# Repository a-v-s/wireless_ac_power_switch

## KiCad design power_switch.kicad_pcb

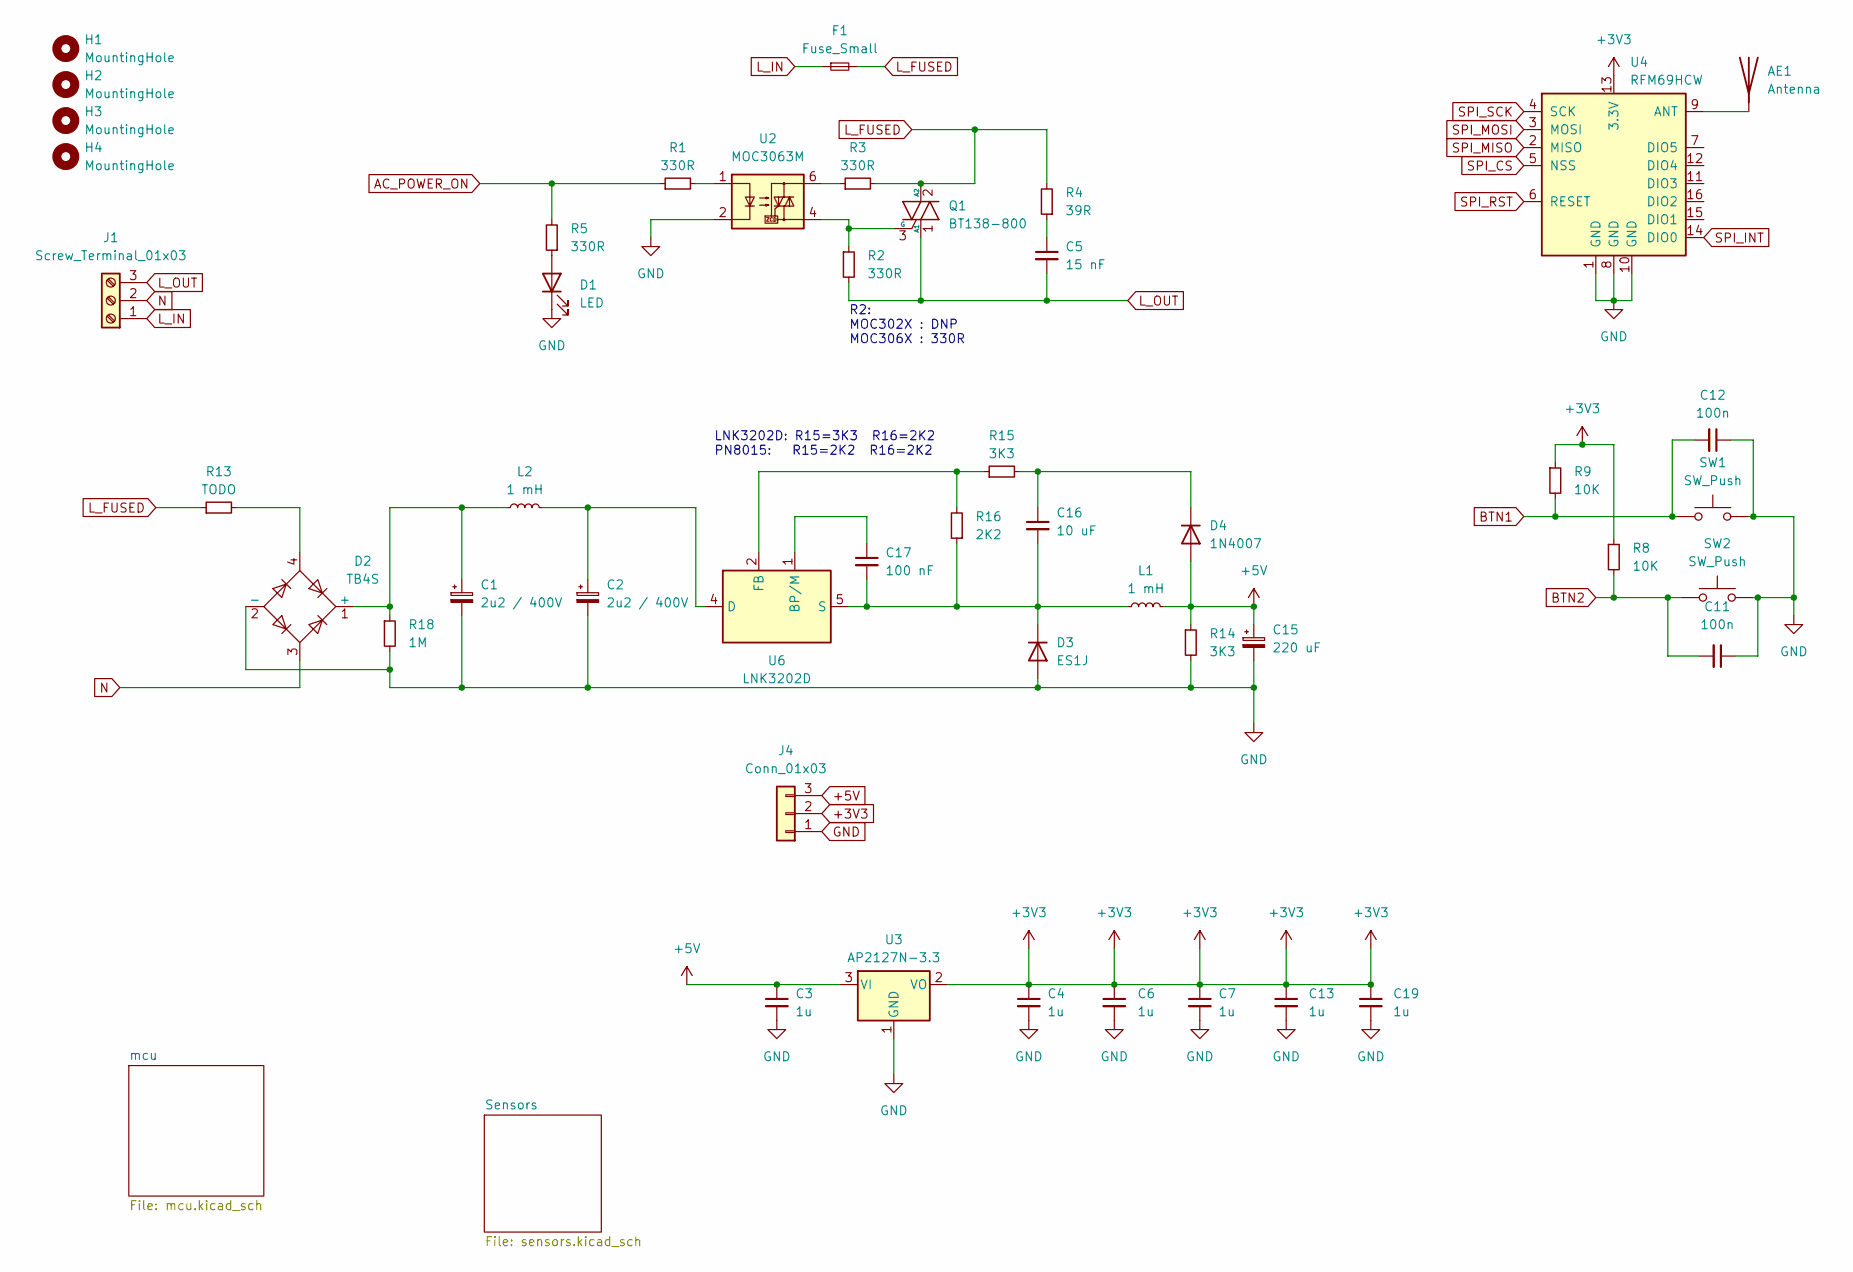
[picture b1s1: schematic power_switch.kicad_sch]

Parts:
AE1: Antenna; TestPoint_THTPad_D2.0mm_Drill1.0mm
C1, C2: 2u2 / 400V; CP_Elec_6.3x5.4
C3, C4, C6, C7, C13, C19: 1u; C_0805_2012Metric
C5: 15 nF; C_Rect_L11.0mm_W4.2mm_P10.00mm_MKT
C11, C12: 100n; C_0805_2012Metric
C15: 220 uF; CP_Elec_6.3x5.4
C16: 10 uF; C_0805_2012Metric
C17: 100 nF; C_0805_2012Metric
D1: LED; LED_0805_2012Metric
D2: TB4S; Diode_Bridge_Diotec_ABS
D3: ES1J; D_SMA
D4: 1N4007; D_SMA
F1: Fuse_Small; Fuseholder_Cylinder-5x20mm_Stelvio-Kontek_PTF78_Horizontal_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
H1, H2, H3, H4: MountingHole; MountingHole_2.2mm_M2
J1: Screw_Terminal_01x03; TerminalBlock_bornier-3_P5.08mm
J4: Conn_01x03; PinHeader_1x03_P2.54mm_Vertical
L1, L2: 1 mH; L_Changjiang_FNR8065S
Q1: BT138-800; TO-220-3_Vertical
R1, R5: 330R; R_0805_2012Metric
R2, R3: 330R; R_Axial_DIN0207_L6.3mm_D2.5mm_P10.16mm_Horizontal
R4: 39R; R_Axial_DIN0207_L6.3mm_D2.5mm_P10.16mm_Horizontal
R8, R9: 10K; R_0805_2012Metric
R13: TODO; R_Axial_DIN0309_L9.0mm_D3.2mm_P2.54mm_Vertical
R14, R15: 3K3; R_0805_2012Metric
R16: 2K2; R_0805_2012Metric
R18: 1M; R_1206_3216Metric
SW1, SW2: SW_Push; TS-1187
U2: MOC3063M; DIP-6_W7.62mm
U3: AP2127N-3.3; SOT-23
U4: RFM69HCW; HOPERF_RFM9XW_SMD
U6: LNK3202D; PowerIntegrations_SO-8C

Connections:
+3V3: C4.1, C6.1, C7.1, C13.1, C19.1, J4.2, R8.1, R9.1, U3.2 (VO), U4.13 (3.3V); also elsewhere on the board
+5V: C3.1, C15.1, D4.2 (A), J4.3, L1.2, R14.1, U3.3 (VI)
AC_POWER_ON: R1.1, R5.2; also elsewhere on the board
BTN1: C12.2, R9.2, SW1.2; also elsewhere on the board
BTN2: C11.2, R8.2, SW2.2; also elsewhere on the board
GND: C1.2, C2.2, C3.2, C4.2, C6.2, C7.2, C11.1, C12.1, C13.2, C15.2, C19.2, D1.1 (K), D2.2 (-), D3.2 (A), J4.1, R14.2, R18.2, SW1.1, SW2.1, U2.2, U3.1 (GND), U4.1 (GND), U4.8 (GND), U4.10 (GND); also elsewhere on the board
L_FUSED: F1.2, Q1.2 (A2), R3.2, R4.2, R13.1
L_IN: F1.1, J1.1
L_OUT: C5.2, J1.3, Q1.1 (A1), R2.2
N: D2.3, J1.2
unnamed: AE1.1 (A), U4.9 (ANT)
unnamed: C5.1, R4.1
unnamed: D1.2 (A), R5.1
unnamed: C1.1, D2.1 (+), L2.1, R18.1
unnamed: D2.4, R13.2
unnamed: C16.2, C17.2, D3.1 (K), L1.1, R16.1, U6.5 (S), U6.6 (S), U6.7 (S), U6.8 (S)
unnamed: C16.1, D4.1 (K), R15.2
unnamed: Q1.3 (G), R2.1, U2.4
unnamed: R1.2, U2.1
unnamed: R3.1, U2.6
unnamed: C17.1, U6.1 (BP/M)
unnamed: C2.1, L2.2, U6.4 (D)
unnamed: R15.1, R16.2, U6.2 (FB)
SPI_CS: U4.5 (NSS); also elsewhere on the board
SPI_INT: U4.14 (DIO0); also elsewhere on the board
SPI_MISO: U4.2 (MISO); also elsewhere on the board
SPI_MOSI: U4.3 (MOSI); also elsewhere on the board
SPI_RST: U4.6 (RESET); also elsewhere on the board
SPI_SCK: U4.4 (SCK); also elsewhere on the board

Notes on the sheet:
R2: MOC302X : DNP MOC306X : 330R
LNK3202D: R15=3K3 R16=2K2 PN8015: R15=2K2 R16=2K2

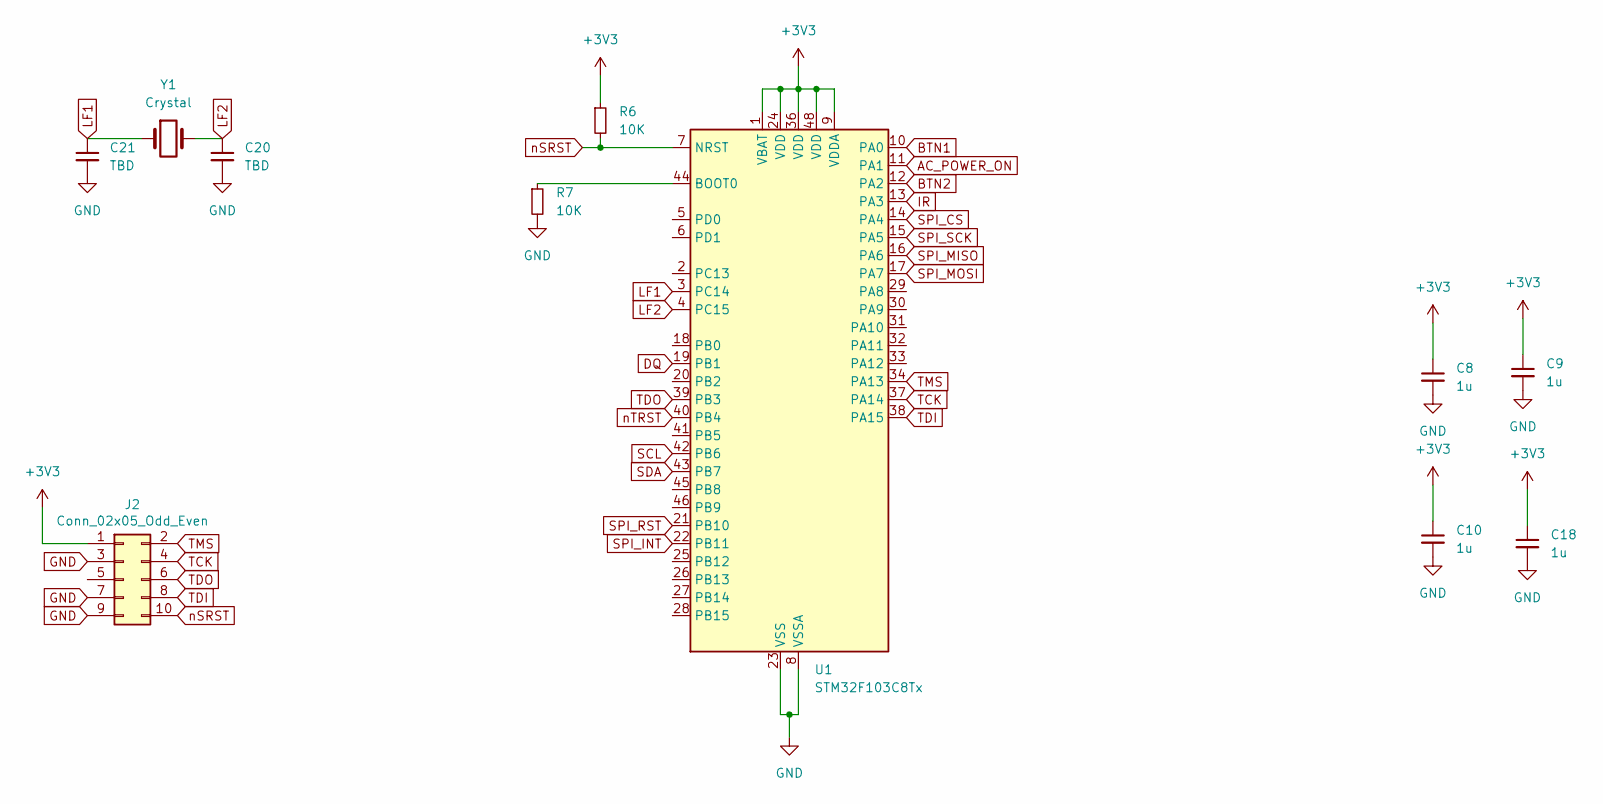
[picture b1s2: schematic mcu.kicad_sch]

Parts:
C8, C9, C10, C18: 1u; C_0805_2012Metric
C20, C21: TBD; C_0805_2012Metric
J2: Conn_02x05_Odd_Even; PinHeader_2x05_P1.27mm_Vertical_SMD
R6, R7: 10K; R_0805_2012Metric
U1: STM32F103C8Tx; LQFP-48_7x7mm_P0.5mm
Y1: Crystal; Crystal_SMD_3215-2Pin_3.2x1.5mm

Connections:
+3V3: C8.1, C9.1, C10.1, C18.1, J2.1, R6.1, U1.1 (VBAT), U1.9 (VDDA), U1.24 (VDD), U1.36 (VDD), U1.48 (VDD); also elsewhere on the board
AC_POWER_ON: U1.11 (PA1); also elsewhere on the board
BTN1: U1.10 (PA0); also elsewhere on the board
BTN2: U1.12 (PA2); also elsewhere on the board
DQ: U1.19 (PB1); also elsewhere on the board
GND: C8.2, C9.2, C10.2, C18.2, C20.2, C21.2, J2.3, J2.7, J2.9, R7.2, U1.8 (VSSA), U1.23 (VSS), U1.35 (VSS), U1.47 (VSS); also elsewhere on the board
IR: U1.13 (PA3); also elsewhere on the board
LF1: C21.1, U1.3 (PC14), Y1.1
LF2: C20.1, U1.4 (PC15), Y1.2
unnamed: R7.1, U1.44 (BOOT0)
SCL: U1.42 (PB6); also elsewhere on the board
SDA: U1.43 (PB7); also elsewhere on the board
SPI_CS: U1.14 (PA4); also elsewhere on the board
SPI_INT: U1.22 (PB11); also elsewhere on the board
SPI_MISO: U1.16 (PA6); also elsewhere on the board
SPI_MOSI: U1.17 (PA7); also elsewhere on the board
SPI_RST: U1.21 (PB10); also elsewhere on the board
SPI_SCK: U1.15 (PA5); also elsewhere on the board
TCK: J2.4, U1.37 (PA14)
TDI: J2.8, U1.38 (PA15)
TDO: J2.6, U1.39 (PB3)
TMS: J2.2, U1.34 (PA13)
nSRST: J2.10, R6.2, U1.7 (NRST)
nTRST: U1.40 (PB4)

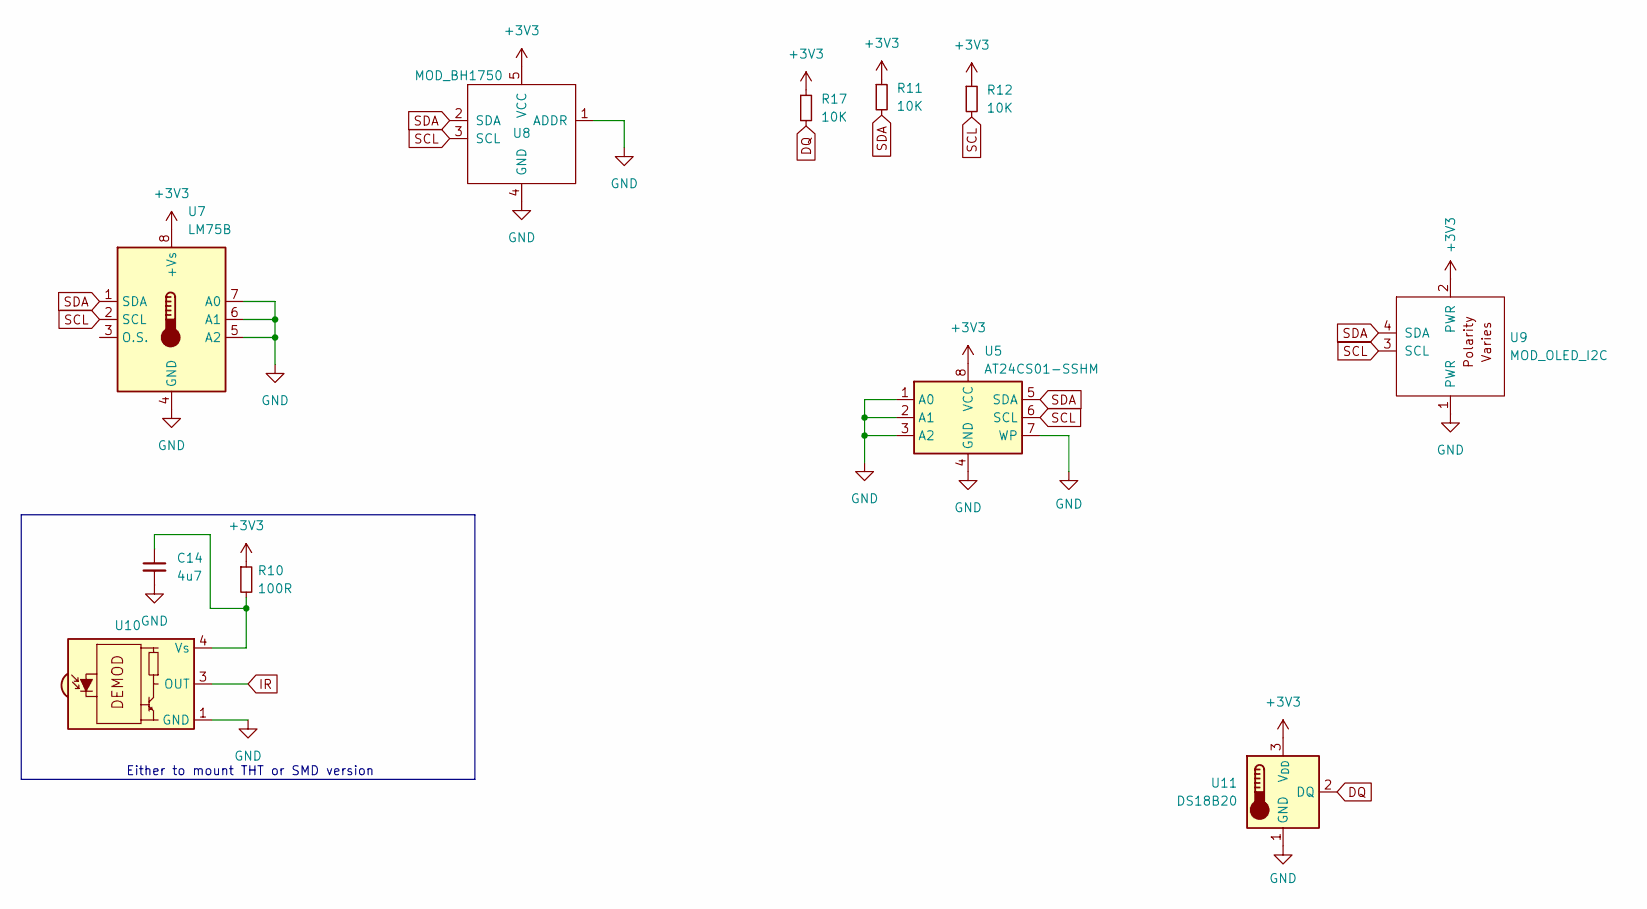
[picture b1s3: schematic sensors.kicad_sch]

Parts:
C14: 4u7; C_0805_2012Metric
R10: 100R; R_0805_2012Metric
R11, R12, R17: 10K; R_0805_2012Metric
U5: AT24CS01-SSHM; SOIC-8_3.9x4.9mm_P1.27mm
U7: LM75B; SO-8_3.9x4.9mm_P1.27mm
U8: MOD_BH1750
U9: MOD_OLED_I2C; MOD_OLED_I2C_128x64_0.96
U10: IRM-H6XXT-TR2
U11: DS18B20; TO-92_Inline

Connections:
+3V3: R10.1, R11.1, R12.1, R17.1, U5.8 (VCC), U7.8 (+Vs), U8.5 (VCC), U9.2 (PWR), U11.3 (V_{DD}); also elsewhere on the board
DQ: R17.2, U11.2 (DQ); also elsewhere on the board
GND: C14.2, U5.1 (A0), U5.2 (A1), U5.3 (A2), U5.4 (GND), U5.7 (WP), U7.4 (GND), U7.5 (A2), U7.6 (A1), U7.7 (A0), U8.1 (ADDR), U8.4 (GND), U9.1 (PWR), U10.1 (GND), U10.2 (GND), U11.1 (GND); also elsewhere on the board
IR: U10.3 (OUT); also elsewhere on the board
unnamed: C14.1, R10.2, U10.4 (Vs)
SCL: R12.2, U5.6 (SCL), U7.2 (SCL), U8.3 (SCL), U9.3 (SCL); also elsewhere on the board
SDA: R11.2, U5.5 (SDA), U7.1 (SDA), U8.2 (SDA), U9.4 (SDA); also elsewhere on the board

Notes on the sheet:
Either to mount THT or SMD version

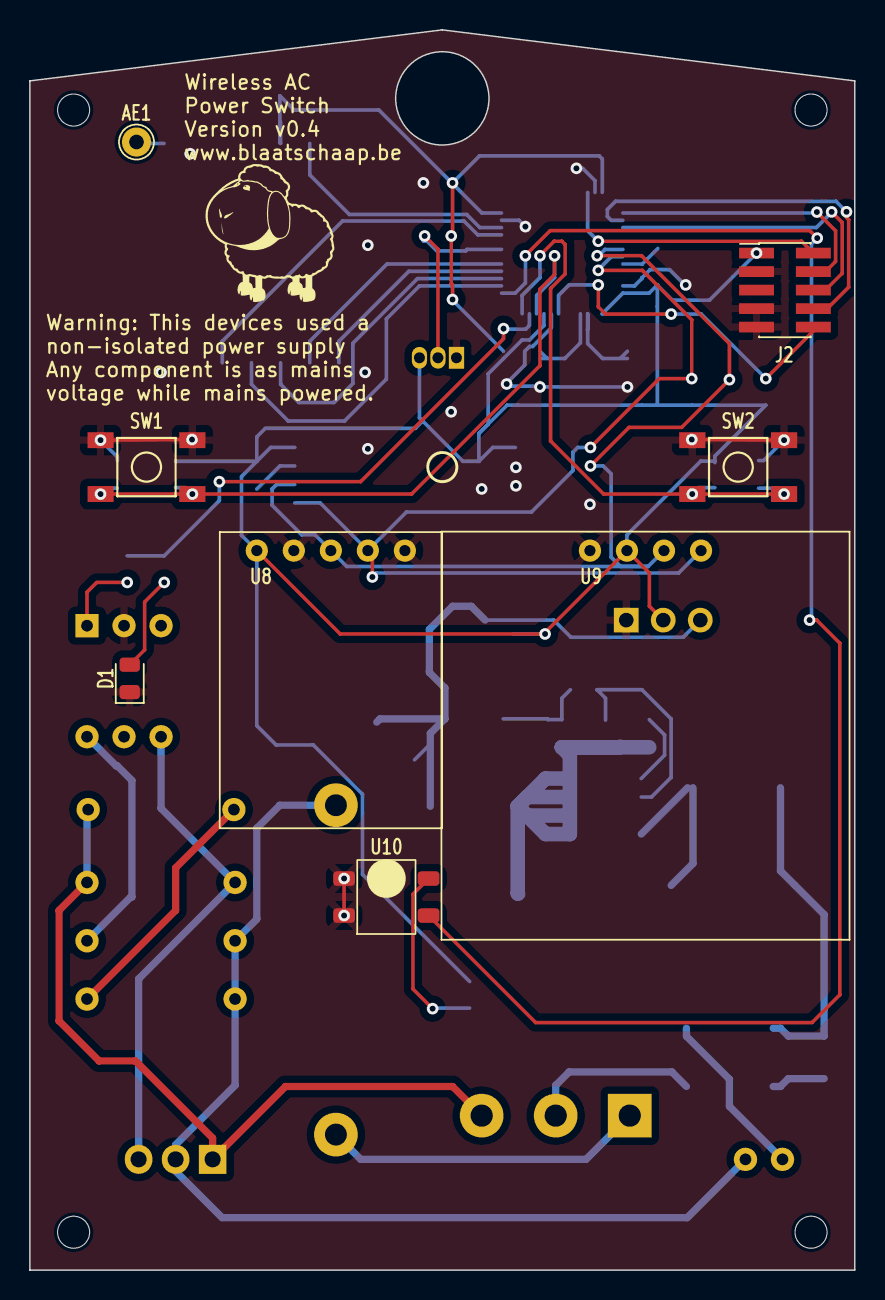
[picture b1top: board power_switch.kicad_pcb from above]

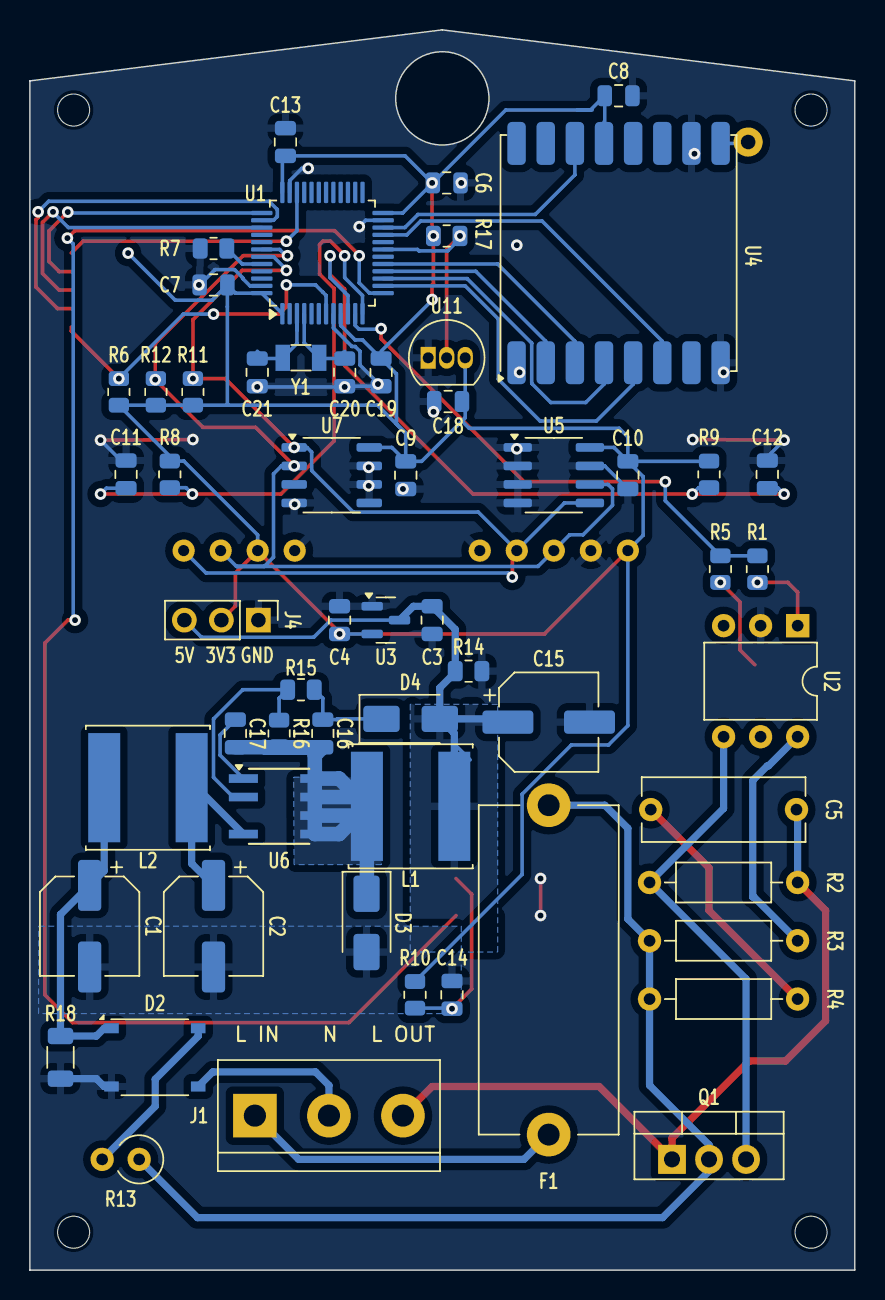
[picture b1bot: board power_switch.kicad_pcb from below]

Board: 2 copper layers, 56.6 x 85.1 mm, 69 parts (57 on the bottom side), 42 nets.

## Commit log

2023-12-31 RF AC Power Switch v0.1
2024-01-12 Changes from initial results (dimentions, foorprints)
2024-02-03 W.I.P.
2024-03-01 so far, changes to be made to schematic again
2024-03-01 adding display
2024-03-02 Routed
2024-03-03 r/c with ir
2024-03-18 Add i2c header, remove solder jumpers for display polarity
2024-03-18 v0.3
2024-04-06 Add missing values
2024-09-02 acdc wip
2024-09-06 so far
2024-09-06 one can go
2024-09-06 Working on flipping all
2024-09-07 initial routing done
2024-09-07 backups
2024-09-08 Adding a bleeding resistor
2024-09-11 v0.4
